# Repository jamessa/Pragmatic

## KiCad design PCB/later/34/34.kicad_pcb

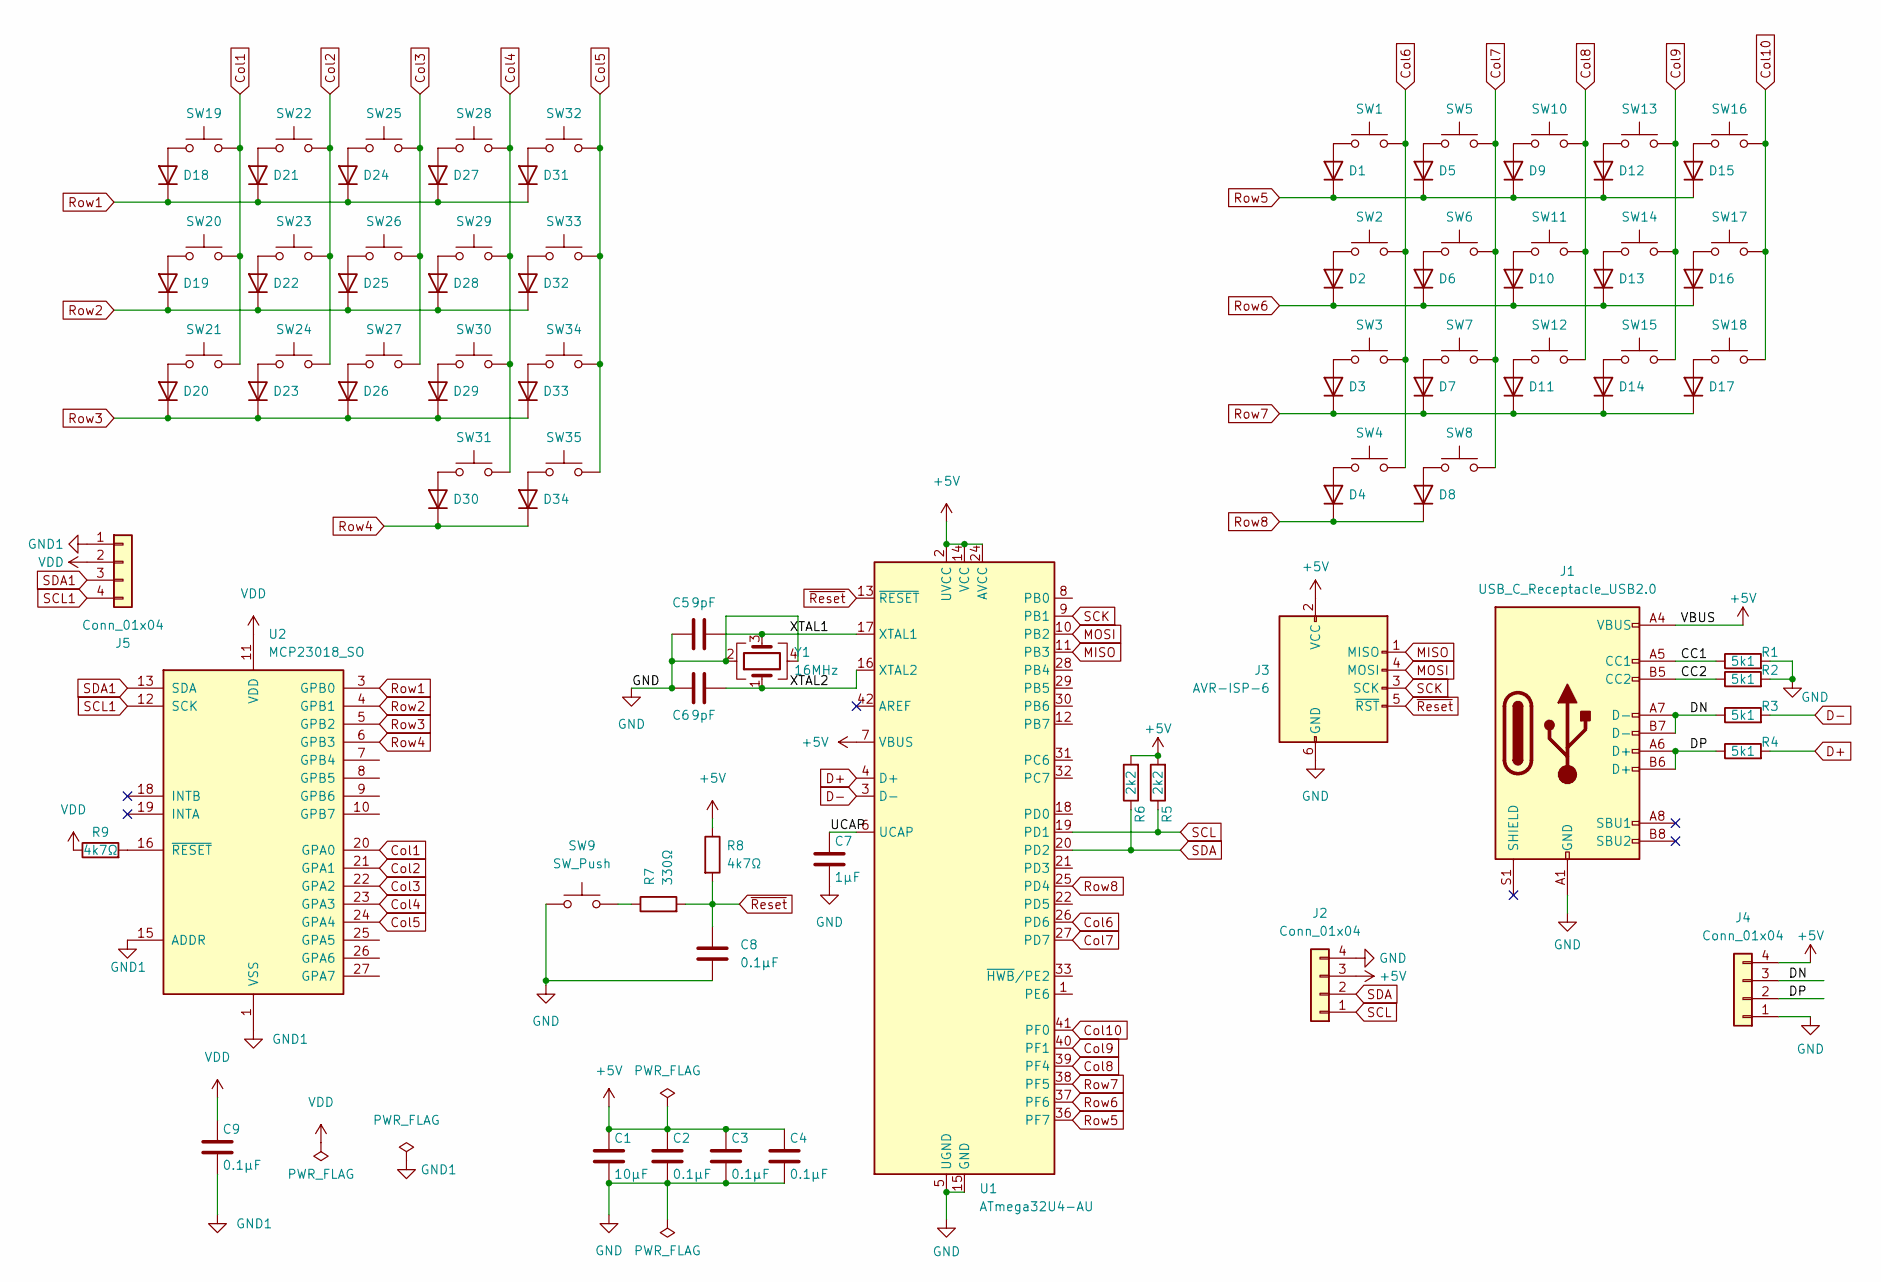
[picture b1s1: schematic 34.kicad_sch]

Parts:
C1: 10µF; C_0603_1608Metric_Pad1.08x0.95mm_HandSolder
C2, C3, C4, C8, C9: 0.1µF; C_0402_1005Metric_Pad0.74x0.62mm_HandSolder
C5, C6: 9pF; C_0402_1005Metric_Pad0.74x0.62mm_HandSolder
C7: 1µF; C_0402_1005Metric_Pad0.74x0.62mm_HandSolder
D1, D2, D3, D4, D5, D6, D7, D8, D9, D10, D11, D12, D13, D14, D15, D16, D17, D18, D19, D20, D21, D22, D23, D24, D25, D26, D27, D28, D29, D30, D31, D32, D33, D34: 1N4148; D3_SMD_v2; LCSC C81598
J1: USB_C_Receptacle_USB2.0; USB_C_Receptacle_HRO_TYPE-C-31-M-12; LCSC C165948
J2, J5: Conn_01x04; JST_PH_S4B-PH-K_1x04_P2.00mm_Horizontal; LCSC C265452
J3: AVR-ISP-6; PinHeader_2x03_P2.54mm_Vertical
J4: Conn_01x04; USB wire pad
R1, R2, R3, R4: 5k1; R_0402_1005Metric_Pad0.72x0.64mm_HandSolder
R5, R6: 2k2; R_0402_1005Metric_Pad0.72x0.64mm_HandSolder
R7: 330Ω; R_0402_1005Metric_Pad0.72x0.64mm_HandSolder
R8, R9: 4k7Ω; R_0402_1005Metric_Pad0.72x0.64mm_HandSolder
SW1, SW2, SW3, SW4, SW5, SW6, SW7, SW8, SW10, SW11, SW12, SW13, SW14, SW15, SW16, SW17, SW18, SW19, SW20, SW21, SW22, SW23, SW24, SW25, SW26, SW27, SW28, SW29, SW30, SW31, SW32, SW33, SW34, SW35: SW_Push; MX_Hotswap_Choc_Solder
SW9: SW_Push; SW_SPST_SKQG_WithStem
U1: ATmega32U4-AU; TQFP-44_10x10mm_P0.8mm
U2: MCP23018_SO; SOIC-28W_7.5x17.9mm_P1.27mm
Y1: 16MHz; Crystal_SMD_3225-4Pin_3.2x2.5mm; LCSC C13738

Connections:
+5V: C1.1, C2.1, C3.1, C4.1, J1.A4 (VBUS), J1.A9 (VBUS), J1.B4 (VBUS), J1.B9 (VBUS), J2.3, J3.2 (VCC), J4.4, R5.2, R6.2, R8.1, U1.2 (UVCC), U1.7 (VBUS), U1.14 (VCC), U1.24 (AVCC), U1.34 (VCC), U1.44 (AVCC)
/CC1: J1.A5 (CC1), R1.1
/CC2: J1.B5 (CC2), R2.1
/DN: J1.A7 (D-), J1.B7 (D-), J4.3, R3.1
/DP: J1.A6 (D+), J1.B6 (D+), J4.2, R4.1
/UCAP: C7.1, U1.6 (UCAP)
/XTAL1: C5.2, U1.17 (XTAL1), Y1.3
/XTAL2: C6.2, U1.16 (XTAL2), Y1.1
Col1: SW19.2, SW20.2, SW21.2, U2.20 (GPA0)
Col2: SW22.2, SW23.2, SW24.2, U2.21 (GPA1)
Col3: SW25.2, SW26.2, SW27.2, U2.22 (GPA2)
Col4: SW28.2, SW29.2, SW30.2, SW31.2, U2.23 (GPA3)
Col5: SW32.2, SW33.2, SW34.2, SW35.2, U2.24 (GPA4)
Col6: SW1.2, SW2.2, SW3.2, SW4.2, U1.26 (PD6)
Col7: SW5.2, SW6.2, SW7.2, SW8.2, U1.27 (PD7)
Col8: SW10.2, SW11.2, SW12.2, U1.39 (PF4)
Col9: SW13.2, SW14.2, SW15.2, U1.40 (PF1)
Col10: SW16.2, SW17.2, SW18.2, U1.41 (PF0)
D+: R4.2, U1.4 (D+)
D-: R3.2, U1.3 (D-)
GND: C1.2, C2.2, C3.2, C4.2, C5.1, C6.1, C7.2, C8.2, J1.A1 (GND), J1.A12 (GND), J1.B1 (GND), J1.B12 (GND), J2.4, J3.6 (GND), J4.1, R1.2, R2.2, SW9.1, U1.5 (UGND), U1.15 (GND), U1.23 (GND), U1.35 (GND), U1.43 (GND), Y1.2, Y1.4
GND1: C9.2, J5.1, U2.1 (VSS), U2.15 (ADDR)
MISO: J3.1 (MISO), U1.11 (PB3)
MOSI: J3.4 (MOSI), U1.10 (PB2)
unnamed: D1.2 (A), SW1.1
unnamed: D2.2 (A), SW2.1
unnamed: D3.2 (A), SW3.1
unnamed: D4.2 (A), SW4.1
unnamed: D5.2 (A), SW5.1
unnamed: D6.2 (A), SW6.1
unnamed: D7.2 (A), SW7.1
unnamed: D8.2 (A), SW8.1
unnamed: D9.2 (A), SW10.1
unnamed: D10.2 (A), SW11.1
unnamed: D11.2 (A), SW12.1
unnamed: D12.2 (A), SW13.1
unnamed: D13.2 (A), SW14.1
unnamed: D14.2 (A), SW15.1
unnamed: D15.2 (A), SW16.1
unnamed: D16.2 (A), SW17.1
unnamed: D17.2 (A), SW18.1
unnamed: D18.2 (A), SW19.1
unnamed: D19.2 (A), SW20.1
unnamed: D20.2 (A), SW21.1
unnamed: D21.2 (A), SW22.1
unnamed: D22.2 (A), SW23.1
unnamed: D23.2 (A), SW24.1
unnamed: D24.2 (A), SW25.1
unnamed: D25.2 (A), SW26.1
unnamed: D26.2 (A), SW27.1
unnamed: D27.2 (A), SW28.1
unnamed: D28.2 (A), SW29.1
unnamed: D29.2 (A), SW30.1
unnamed: D30.2 (A), SW31.1
unnamed: D31.2 (A), SW32.1
unnamed: D32.2 (A), SW33.1
unnamed: D33.2 (A), SW34.1
unnamed: D34.2 (A), SW35.1
unnamed: R7.1, SW9.2
unnamed: R9.2, U2.16 (~RESET)
Row1: D18.1 (K), D21.1 (K), D24.1 (K), D27.1 (K), D31.1 (K), U2.3 (GPB0)
Row2: D19.1 (K), D22.1 (K), D25.1 (K), D28.1 (K), D32.1 (K), U2.4 (GPB1)
Row3: D20.1 (K), D23.1 (K), D26.1 (K), D29.1 (K), D33.1 (K), U2.5 (GPB2)
Row4: D30.1 (K), D34.1 (K), U2.6 (GPB3)
Row5: D1.1 (K), D5.1 (K), D9.1 (K), D12.1 (K), D15.1 (K), U1.36 (PF7)
Row6: D2.1 (K), D6.1 (K), D10.1 (K), D13.1 (K), D16.1 (K), U1.37 (PF6)
Row7: D3.1 (K), D7.1 (K), D11.1 (K), D14.1 (K), D17.1 (K), U1.38 (PF5)
Row8: D4.1 (K), D8.1 (K), U1.25 (PD4)
SCK: J3.3 (SCK), U1.9 (PB1)
SCL: J2.1, R6.1, U1.19 (PD1)
SCL1: J5.4, U2.12 (SCK)
SDA: J2.2, R5.1, U1.20 (PD2)
SDA1: J5.3, U2.13 (SDA)
VDD: C9.1, J5.2, R9.1, U2.11 (VDD)
~Reset: C8.1, J3.5 (~RST), R7.2, R8.2, U1.13 (~RESET)

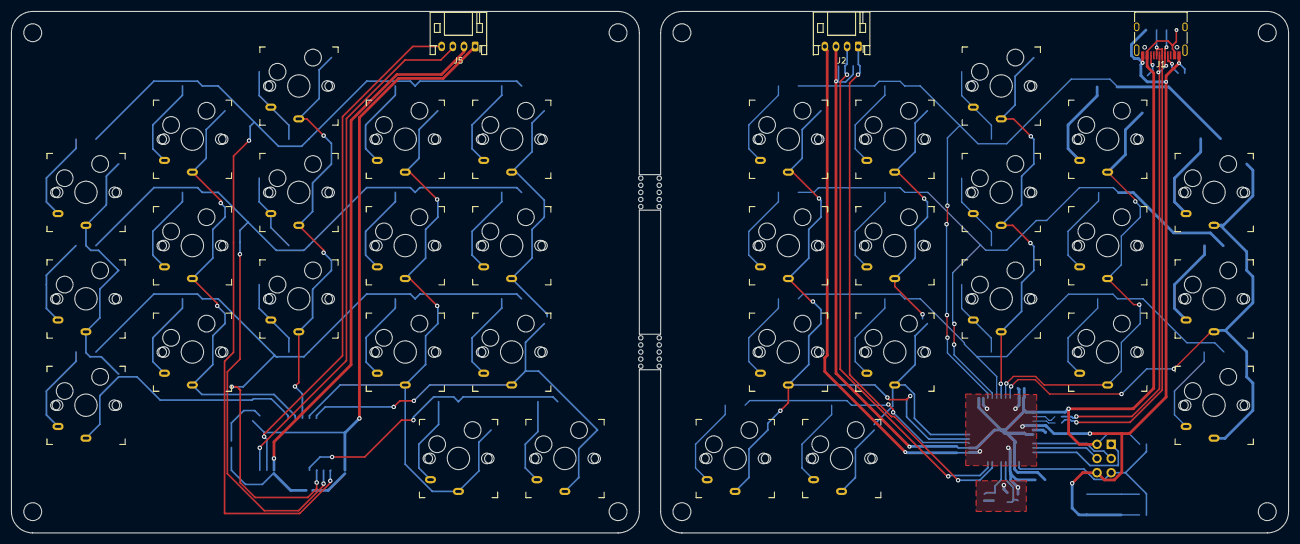
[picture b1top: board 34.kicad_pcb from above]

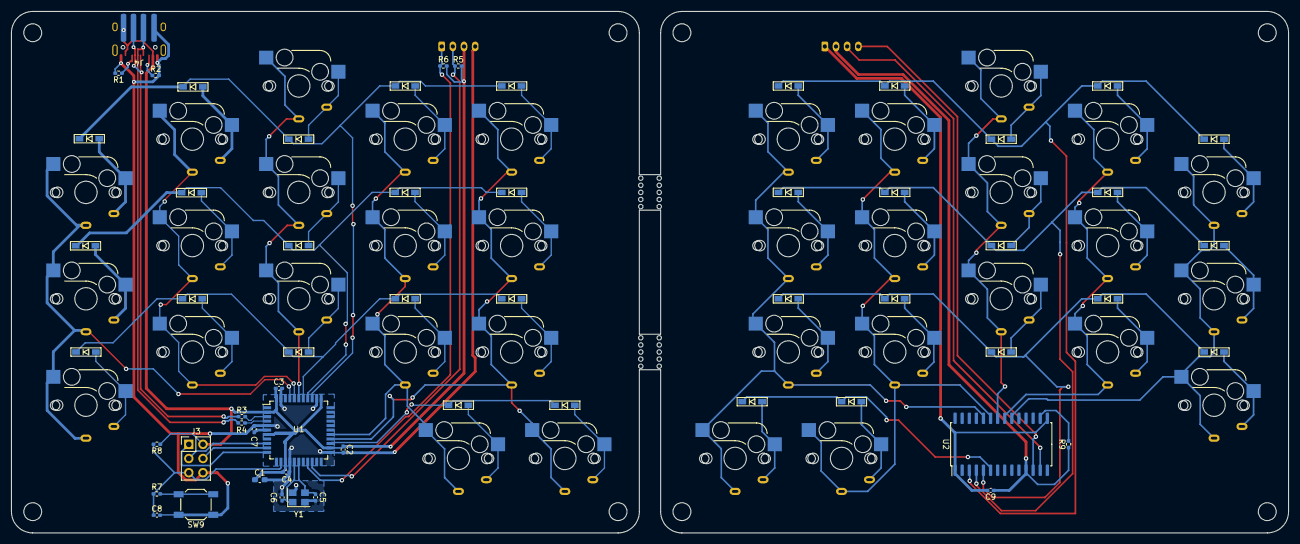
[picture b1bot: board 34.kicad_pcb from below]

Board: 2 copper layers, 228.6 x 93.3 mm, 95 parts (58 on the bottom side), 75 nets.

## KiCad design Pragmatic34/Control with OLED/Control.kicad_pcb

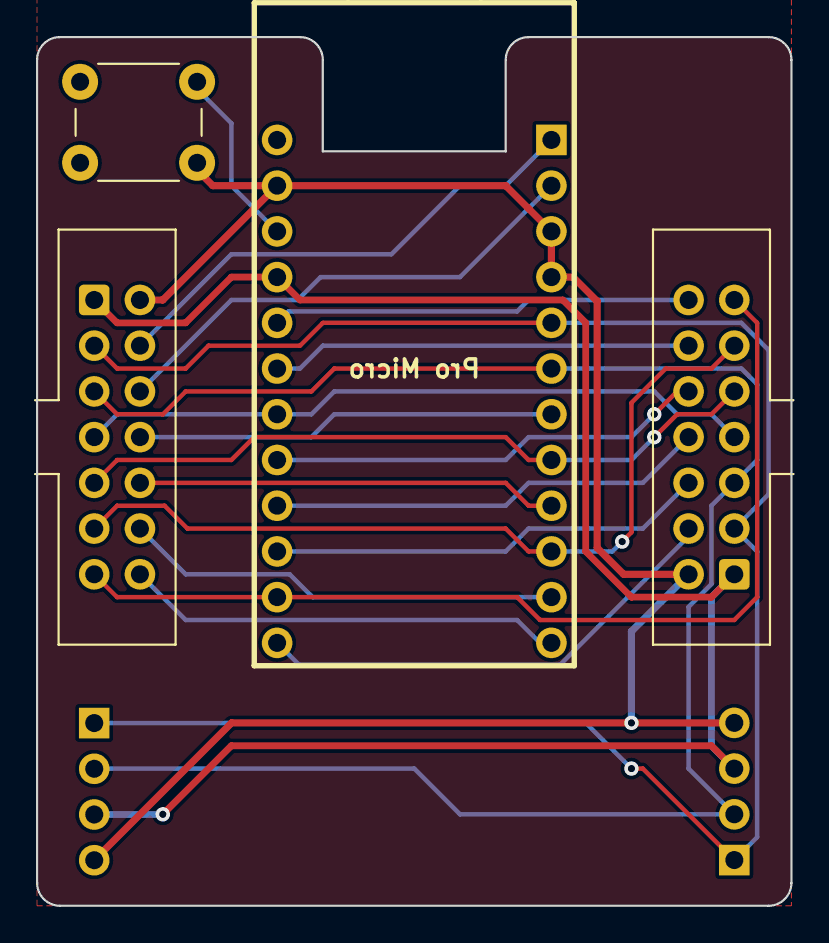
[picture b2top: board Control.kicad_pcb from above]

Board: 2 copper layers, 41.9 x 48.3 mm, 8 parts (1 on the bottom side), 21 nets.

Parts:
J1: L; IDC-Header_2x07_P2.54mm_Vertical
J2: R; IDC-Header_2x07_P2.54mm_Vertical
J3, J4: OLED; SSD1306_OLED-0.91-128x32
L1: JLC Legend
Logo1: OSHW-Symbol_6.7x6mm_Copper
SW1: SW_Push; SW_PUSH_6mm
U1: ProMicro; ProMicro Type C Reversed

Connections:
Col1: J1.4, U1.1 (TX0/PD3)
Col2: J1.6, U1.2 (RX1/PD2)
Col3: J1.8, U1.7 (4/PD4)
Col4: J1.10, U1.9 (6/PD7)
Col5: J1.12, U1.11 (8/PB4)
Col6: J1.14, U1.12 (9/PB5)
Col7: J2.4, U1.13 (10/PB6)
Col8: J2.6, U1.15 (14/PB3)
Col9: J2.8, U1.16 (15/PB1)
Col10: J2.10, U1.17 (A0/PF7)
Col11: J2.12, U1.19 (A2/PF5)
Col12: J2.14, U1.20 (A3/PF4)
GND: J1.2, J2.2, J3.4, J4.4, SW1.2, U1.3 (GND), U1.4 (GND), U1.23 (GND)
Reset: SW1.1, U1.22 (RST)
Row1: J1.3, J2.3, J3.1, J4.1, U1.5 (2/PD1)
Row2: J1.5, J2.5, J3.2, J4.2, U1.6 (3/PD0)
Row3: J1.7, J2.7, U1.18 (A1/PF6)
Row4: J1.9, J2.9, U1.8 (5/PC6)
Row5: J1.11, J2.11, U1.10 (7/PE6)
Row6: J1.13, J2.13, U1.14 (16/PB2)
VCC: J1.1, J2.1, J3.3, J4.3, U1.21 (VCC)

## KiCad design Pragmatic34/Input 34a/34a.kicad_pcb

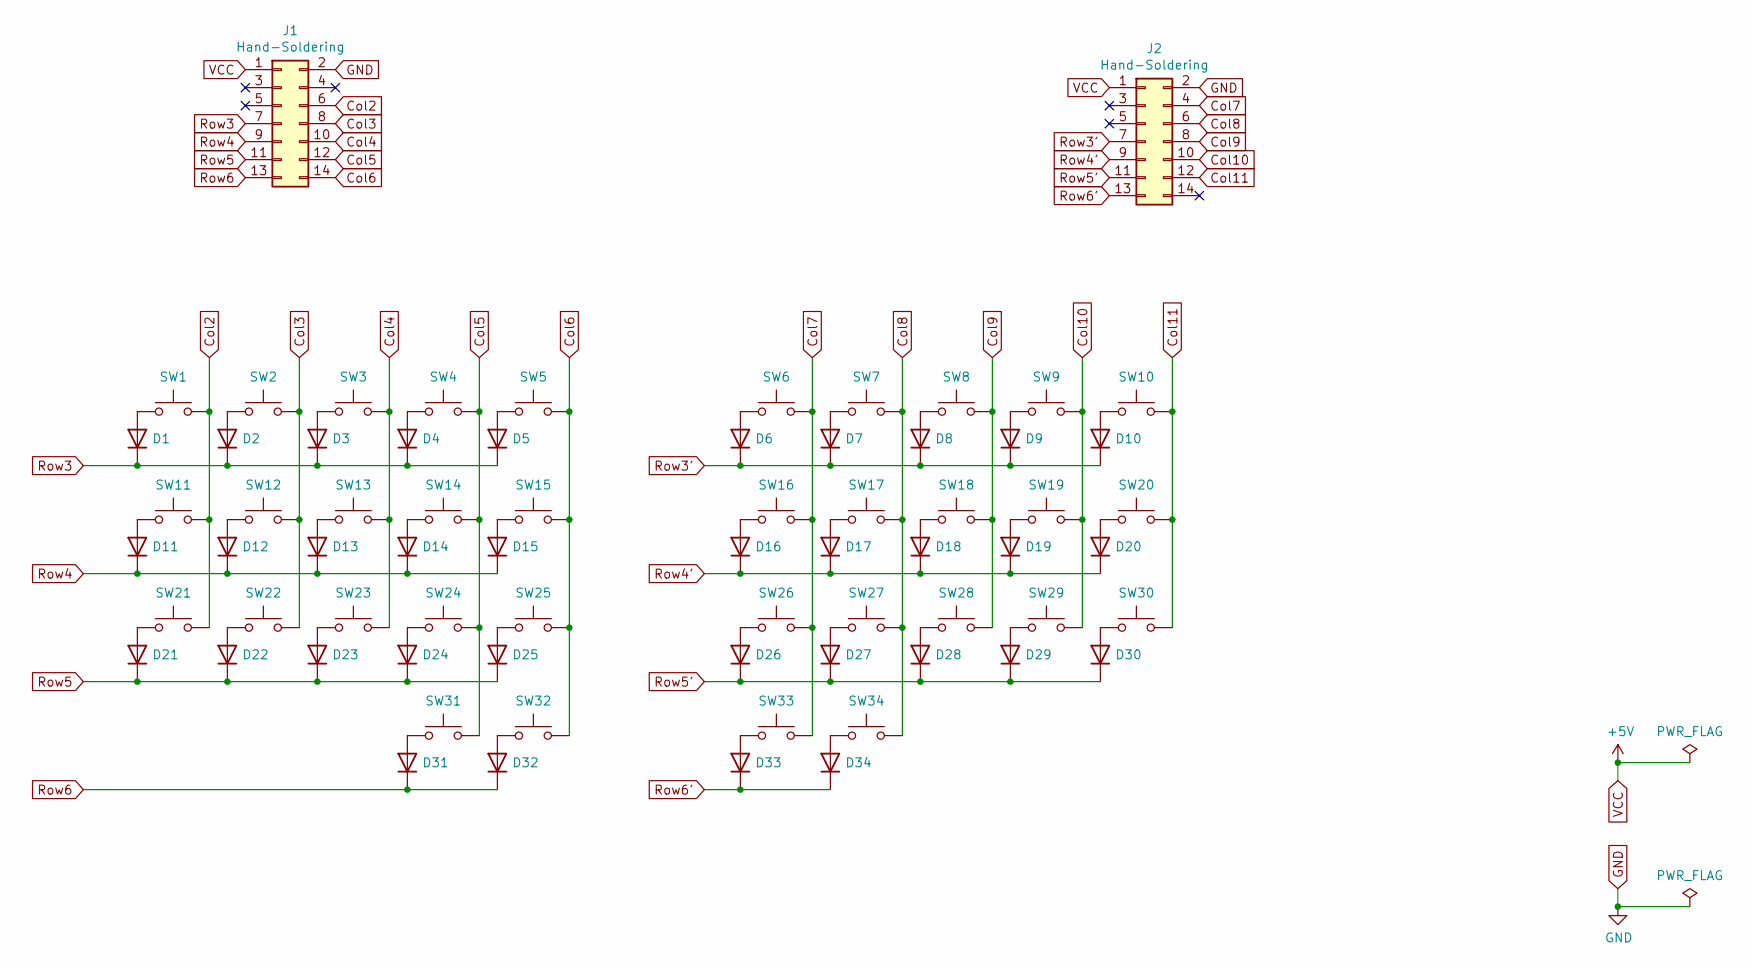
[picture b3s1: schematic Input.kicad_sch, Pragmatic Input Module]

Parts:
D1, D2, D3, D4, D5, D6, D7, D8, D9, D10, D11, D12, D13, D14, D15, D16, D17, D18, D19, D20, D21, D22, D23, D24, D25, D26, D27, D28, D29, D30, D31, D32, D33, D34: 1N4148; D3_SMD_v2; LCSC C81598
J1, J2: Hand-Soldering; IDC-Header_2x07_P2.54mm_Vertical; LCSC C3406
SW1, SW2, SW3, SW4, SW5, SW6, SW7, SW8, SW9, SW10, SW11, SW12, SW13, SW14, SW15, SW16, SW17, SW18, SW19, SW20, SW21, SW22, SW23, SW24, SW25, SW26, SW27, SW28, SW29, SW30, SW31, SW32, SW33, SW34: SW_Push; MX_Hotswap; LCSC C2803348

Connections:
Col2: J1.6, SW1.2, SW11.2, SW21.2
Col3: J1.8, SW2.2, SW12.2, SW22.2
Col4: J1.10, SW3.2, SW13.2, SW23.2; also elsewhere on the board
Col5: J1.12, SW4.2, SW14.2, SW24.2, SW31.2
Col6: J1.14, SW5.2, SW15.2, SW25.2, SW32.2
Col7: J2.4, SW6.2, SW16.2, SW26.2, SW33.2
Col8: J2.6, SW7.2, SW17.2, SW27.2, SW34.2
Col9: J2.8, SW8.2, SW18.2, SW28.2; also elsewhere on the board
Col10: J2.10, SW9.2, SW19.2, SW29.2
Col11: J2.12, SW10.2, SW20.2, SW30.2
GND: J1.2, J2.2
unnamed: D1.2 (A), SW1.1
unnamed: D2.2 (A), SW2.1
unnamed: D3.2 (A), SW3.1
unnamed: D4.2 (A), SW4.1
unnamed: D5.2 (A), SW5.1
unnamed: D6.2 (A), SW6.1
unnamed: D7.2 (A), SW7.1
unnamed: D8.2 (A), SW8.1
unnamed: D9.2 (A), SW9.1
unnamed: D10.2 (A), SW10.1
unnamed: D11.2 (A), SW11.1
unnamed: D12.2 (A), SW12.1
unnamed: D13.2 (A), SW13.1
unnamed: D14.2 (A), SW14.1
unnamed: D15.2 (A), SW15.1
unnamed: D16.2 (A), SW16.1
unnamed: D17.2 (A), SW17.1
unnamed: D18.2 (A), SW18.1
unnamed: D19.2 (A), SW19.1
unnamed: D20.2 (A), SW20.1
unnamed: D21.2 (A), SW21.1
unnamed: D22.2 (A), SW22.1
unnamed: D23.2 (A), SW23.1
unnamed: D24.2 (A), SW24.1
unnamed: D25.2 (A), SW25.1
unnamed: D26.2 (A), SW26.1
unnamed: D27.2 (A), SW27.1
unnamed: D28.2 (A), SW28.1
unnamed: D29.2 (A), SW29.1
unnamed: D30.2 (A), SW30.1
unnamed: D31.2 (A), SW31.1
unnamed: D32.2 (A), SW32.1
unnamed: D33.2 (A), SW33.1
unnamed: D34.2 (A), SW34.1
Row3: D1.1 (K), D2.1 (K), D3.1 (K), D4.1 (K), D5.1 (K), J1.7
Row3': D6.1 (K), D7.1 (K), D8.1 (K), D9.1 (K), D10.1 (K), J2.7
Row4: D11.1 (K), D12.1 (K), D13.1 (K), D14.1 (K), D15.1 (K), J1.9
Row4': D16.1 (K), D17.1 (K), D18.1 (K), D19.1 (K), D20.1 (K), J2.9
Row5: D21.1 (K), D22.1 (K), D23.1 (K), D24.1 (K), D25.1 (K), J1.11
Row5': D26.1 (K), D27.1 (K), D28.1 (K), D29.1 (K), D30.1 (K), J2.11
Row6: D31.1 (K), D32.1 (K), J1.13; also elsewhere on the board
Row6': D33.1 (K), D34.1 (K), J2.13; also elsewhere on the board
VCC: J1.1, J2.1

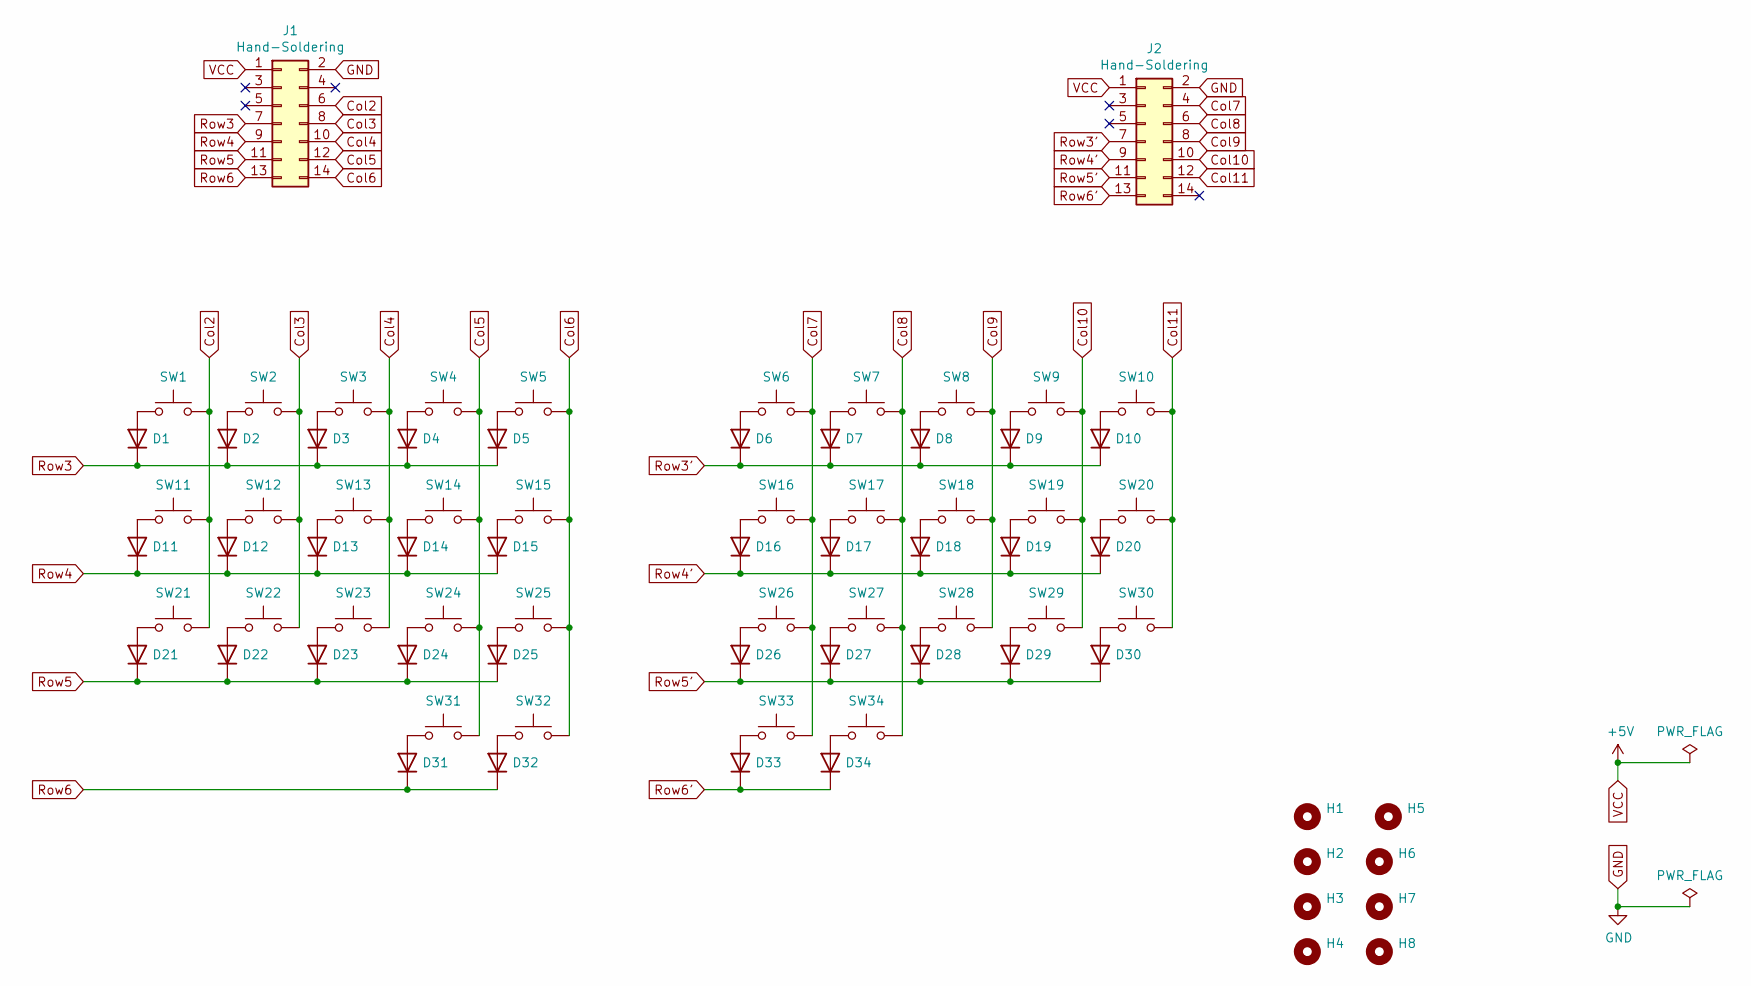
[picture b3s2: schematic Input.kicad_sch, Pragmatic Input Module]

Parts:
D1, D2, D3, D4, D5, D6, D7, D8, D9, D10, D11, D12, D13, D14, D15, D16, D17, D18, D19, D20, D21, D22, D23, D24, D25, D26, D27, D28, D29, D30, D31, D32, D33, D34: 1N4148; D3_SMD_v2; LCSC C81598
H1, H2, H3, H4, H5, H6, H7, H8: MountingHole; MountingHole_2.5mm
J1, J2: Hand-Soldering; IDC-Header_2x07_P2.54mm_Vertical; LCSC C3406
SW1, SW2, SW3, SW4, SW5, SW6, SW7, SW8, SW9, SW10, SW11, SW12, SW13, SW14, SW15, SW16, SW17, SW18, SW19, SW20, SW21, SW22, SW23, SW24, SW25, SW26, SW27, SW28, SW29, SW30, SW31, SW32, SW33, SW34: SW_Push; MX_Hotswap; LCSC C2803348

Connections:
Col2: J1.6, SW1.2, SW11.2, SW21.2
Col3: J1.8, SW2.2, SW12.2, SW22.2
Col4: J1.10, SW3.2, SW13.2, SW23.2; also elsewhere on the board
Col5: J1.12, SW4.2, SW14.2, SW24.2, SW31.2
Col6: J1.14, SW5.2, SW15.2, SW25.2, SW32.2
Col7: J2.4, SW6.2, SW16.2, SW26.2, SW33.2
Col8: J2.6, SW7.2, SW17.2, SW27.2, SW34.2
Col9: J2.8, SW8.2, SW18.2, SW28.2; also elsewhere on the board
Col10: J2.10, SW9.2, SW19.2, SW29.2
Col11: J2.12, SW10.2, SW20.2, SW30.2
GND: J1.2, J2.2
unnamed: D1.2 (A), SW1.1
unnamed: D2.2 (A), SW2.1
unnamed: D3.2 (A), SW3.1
unnamed: D4.2 (A), SW4.1
unnamed: D5.2 (A), SW5.1
unnamed: D6.2 (A), SW6.1
unnamed: D7.2 (A), SW7.1
unnamed: D8.2 (A), SW8.1
unnamed: D9.2 (A), SW9.1
unnamed: D10.2 (A), SW10.1
unnamed: D11.2 (A), SW11.1
unnamed: D12.2 (A), SW12.1
unnamed: D13.2 (A), SW13.1
unnamed: D14.2 (A), SW14.1
unnamed: D15.2 (A), SW15.1
unnamed: D16.2 (A), SW16.1
unnamed: D17.2 (A), SW17.1
unnamed: D18.2 (A), SW18.1
unnamed: D19.2 (A), SW19.1
unnamed: D20.2 (A), SW20.1
unnamed: D21.2 (A), SW21.1
unnamed: D22.2 (A), SW22.1
unnamed: D23.2 (A), SW23.1
unnamed: D24.2 (A), SW24.1
unnamed: D25.2 (A), SW25.1
unnamed: D26.2 (A), SW26.1
unnamed: D27.2 (A), SW27.1
unnamed: D28.2 (A), SW28.1
unnamed: D29.2 (A), SW29.1
unnamed: D30.2 (A), SW30.1
unnamed: D31.2 (A), SW31.1
unnamed: D32.2 (A), SW32.1
unnamed: D33.2 (A), SW33.1
unnamed: D34.2 (A), SW34.1
Row3: D1.1 (K), D2.1 (K), D3.1 (K), D4.1 (K), D5.1 (K), J1.7
Row3': D6.1 (K), D7.1 (K), D8.1 (K), D9.1 (K), D10.1 (K), J2.7
Row4: D11.1 (K), D12.1 (K), D13.1 (K), D14.1 (K), D15.1 (K), J1.9
Row4': D16.1 (K), D17.1 (K), D18.1 (K), D19.1 (K), D20.1 (K), J2.9
Row5: D21.1 (K), D22.1 (K), D23.1 (K), D24.1 (K), D25.1 (K), J1.11
Row5': D26.1 (K), D27.1 (K), D28.1 (K), D29.1 (K), D30.1 (K), J2.11
Row6: D31.1 (K), D32.1 (K), J1.13; also elsewhere on the board
Row6': D33.1 (K), D34.1 (K), J2.13; also elsewhere on the board
VCC: J1.1, J2.1

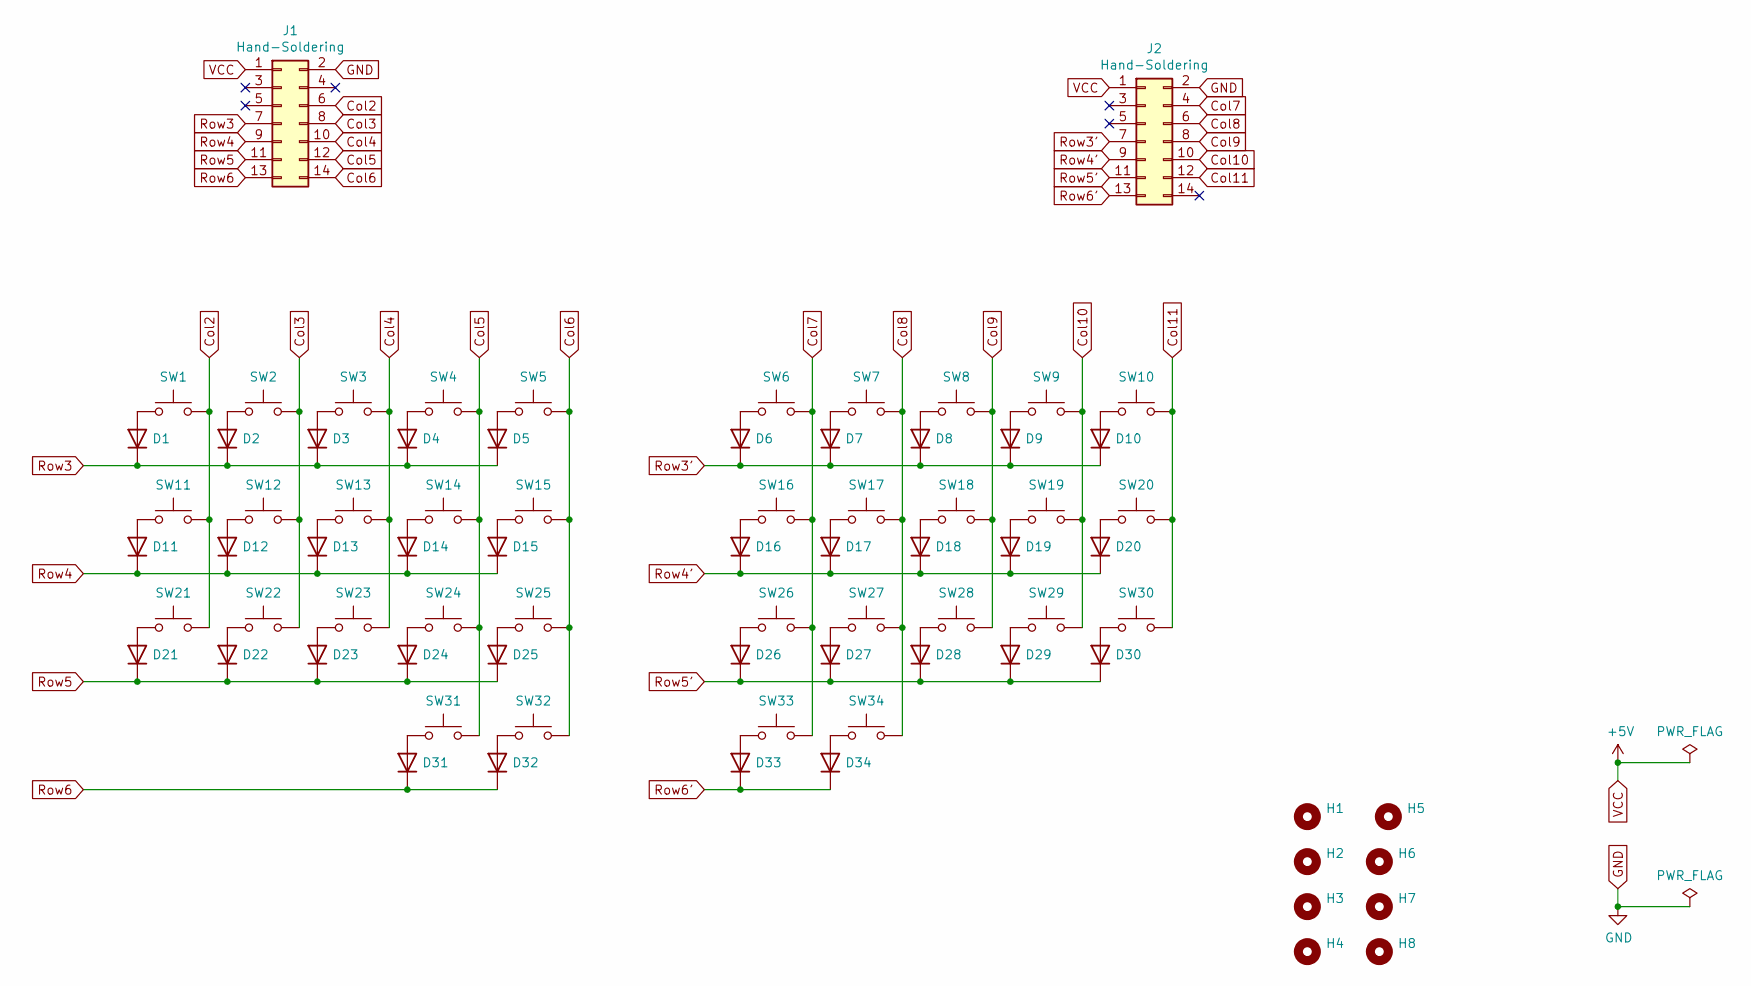
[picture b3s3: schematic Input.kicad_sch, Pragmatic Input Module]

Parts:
D1, D2, D3, D4, D5, D6, D7, D8, D9, D10, D11, D12, D13, D14, D15, D16, D17, D18, D19, D20, D21, D22, D23, D24, D25, D26, D27, D28, D29, D30, D31, D32, D33, D34: 1N4148; D3_SMD_v2; LCSC C81598
H1, H2, H3, H4, H5, H6, H7, H8: MountingHole; MountingHole_2.5mm
J1, J2: Hand-Soldering; IDC-Header_2x07_P2.54mm_Vertical; LCSC C3406
SW1, SW2, SW3, SW4, SW5, SW6, SW7, SW8, SW9, SW10, SW11, SW12, SW13, SW14, SW15, SW16, SW17, SW18, SW19, SW20, SW21, SW22, SW23, SW24, SW25, SW26, SW27, SW28, SW29, SW30, SW31, SW32, SW33, SW34: SW_Push; MX_Hotswap

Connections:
Col2: J1.6, SW1.2, SW11.2, SW21.2
Col3: J1.8, SW2.2, SW12.2, SW22.2
Col4: J1.10, SW3.2, SW13.2, SW23.2; also elsewhere on the board
Col5: J1.12, SW4.2, SW14.2, SW24.2, SW31.2
Col6: J1.14, SW5.2, SW15.2, SW25.2, SW32.2
Col7: J2.4, SW6.2, SW16.2, SW26.2, SW33.2
Col8: J2.6, SW7.2, SW17.2, SW27.2, SW34.2
Col9: J2.8, SW8.2, SW18.2, SW28.2; also elsewhere on the board
Col10: J2.10, SW9.2, SW19.2, SW29.2
Col11: J2.12, SW10.2, SW20.2, SW30.2
GND: J1.2, J2.2
unnamed: D1.2 (A), SW1.1
unnamed: D2.2 (A), SW2.1
unnamed: D3.2 (A), SW3.1
unnamed: D4.2 (A), SW4.1
unnamed: D5.2 (A), SW5.1
unnamed: D6.2 (A), SW6.1
unnamed: D7.2 (A), SW7.1
unnamed: D8.2 (A), SW8.1
unnamed: D9.2 (A), SW9.1
unnamed: D10.2 (A), SW10.1
unnamed: D11.2 (A), SW11.1
unnamed: D12.2 (A), SW12.1
unnamed: D13.2 (A), SW13.1
unnamed: D14.2 (A), SW14.1
unnamed: D15.2 (A), SW15.1
unnamed: D16.2 (A), SW16.1
unnamed: D17.2 (A), SW17.1
unnamed: D18.2 (A), SW18.1
unnamed: D19.2 (A), SW19.1
unnamed: D20.2 (A), SW20.1
unnamed: D21.2 (A), SW21.1
unnamed: D22.2 (A), SW22.1
unnamed: D23.2 (A), SW23.1
unnamed: D24.2 (A), SW24.1
unnamed: D25.2 (A), SW25.1
unnamed: D26.2 (A), SW26.1
unnamed: D27.2 (A), SW27.1
unnamed: D28.2 (A), SW28.1
unnamed: D29.2 (A), SW29.1
unnamed: D30.2 (A), SW30.1
unnamed: D31.2 (A), SW31.1
unnamed: D32.2 (A), SW32.1
unnamed: D33.2 (A), SW33.1
unnamed: D34.2 (A), SW34.1
Row3: D1.1 (K), D2.1 (K), D3.1 (K), D4.1 (K), D5.1 (K), J1.7
Row3': D6.1 (K), D7.1 (K), D8.1 (K), D9.1 (K), D10.1 (K), J2.7
Row4: D11.1 (K), D12.1 (K), D13.1 (K), D14.1 (K), D15.1 (K), J1.9
Row4': D16.1 (K), D17.1 (K), D18.1 (K), D19.1 (K), D20.1 (K), J2.9
Row5: D21.1 (K), D22.1 (K), D23.1 (K), D24.1 (K), D25.1 (K), J1.11
Row5': D26.1 (K), D27.1 (K), D28.1 (K), D29.1 (K), D30.1 (K), J2.11
Row6: D31.1 (K), D32.1 (K), J1.13; also elsewhere on the board
Row6': D33.1 (K), D34.1 (K), J2.13; also elsewhere on the board
VCC: J1.1, J2.1

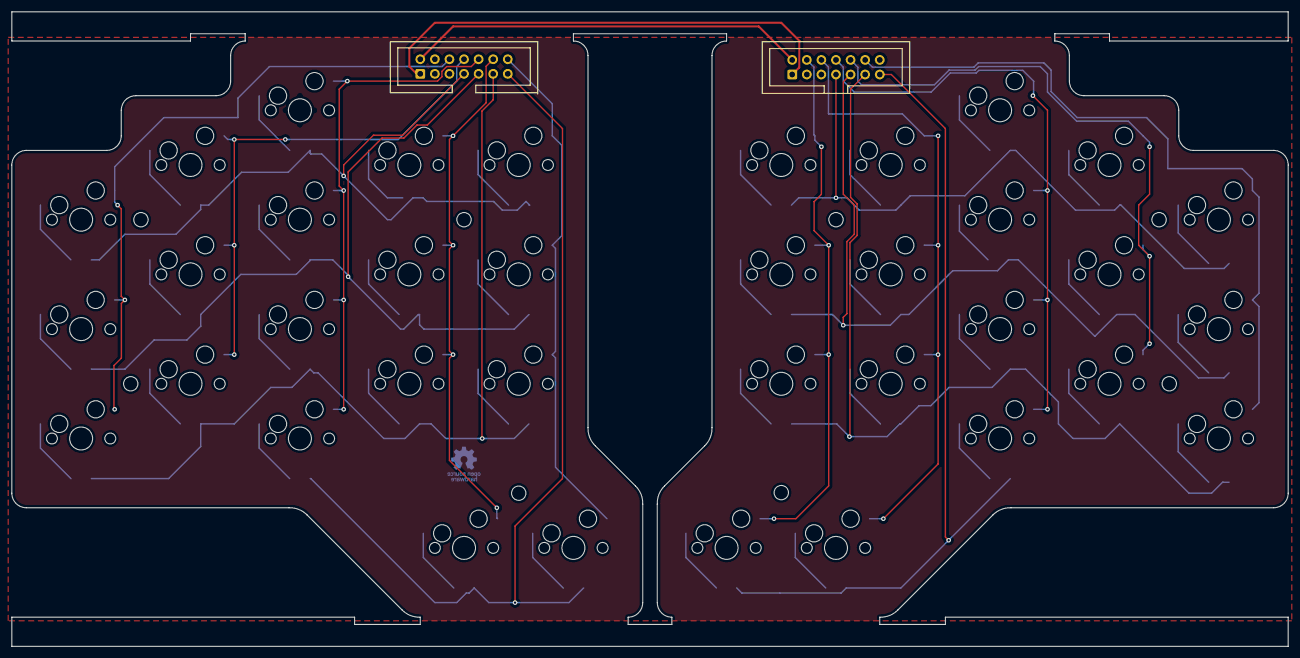
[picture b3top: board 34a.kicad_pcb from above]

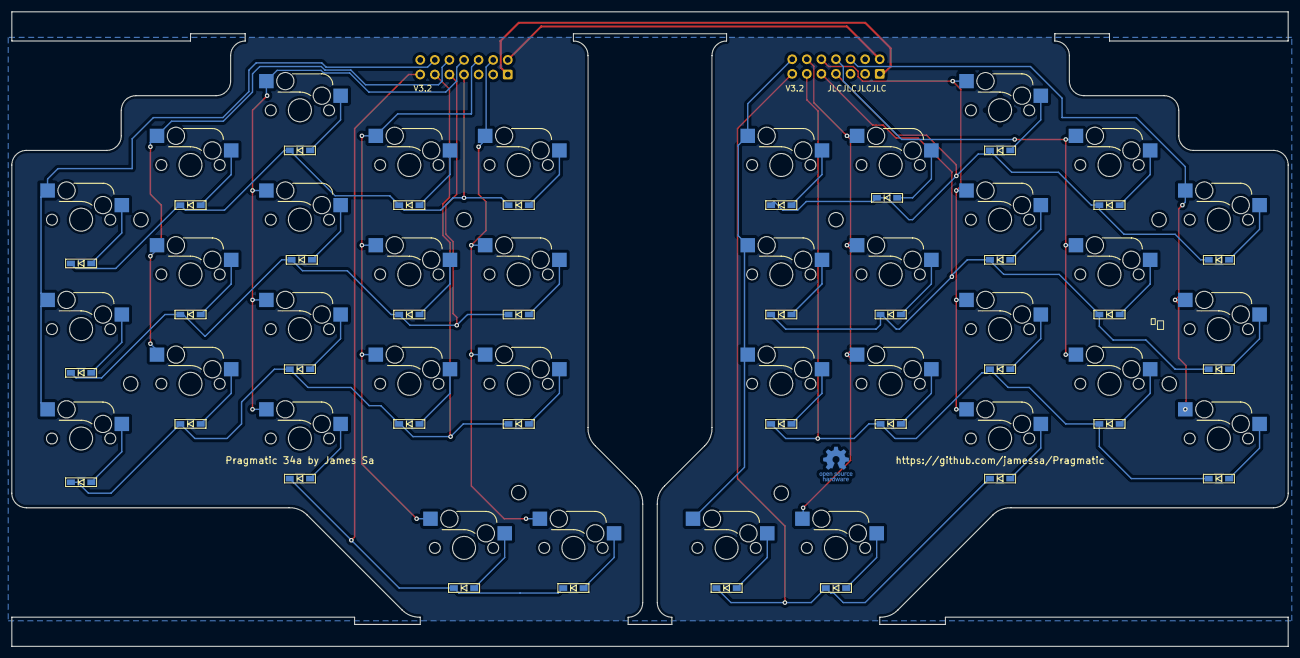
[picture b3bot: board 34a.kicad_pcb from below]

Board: 2 copper layers, 222.2 x 110.5 mm, 83 parts (37 on the bottom side), 56 nets.

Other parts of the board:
D37, D38: 1N4148; D3_SMD_v2
LOGO1: Logo_Open_Hardware_Small; OSHW-Logo_5.7x6mm_Copper
SW37, SW38: SW_Push; MX_Hotswap

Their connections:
Col4: SW37.2; also elsewhere on the board
Col9: SW38.2; also elsewhere on the board
unnamed: D37.2 (A), SW37.1
unnamed: D38.2 (A), SW38.1
Row6: D37.1 (K); also elsewhere on the board
Row6': D38.1 (K); also elsewhere on the board

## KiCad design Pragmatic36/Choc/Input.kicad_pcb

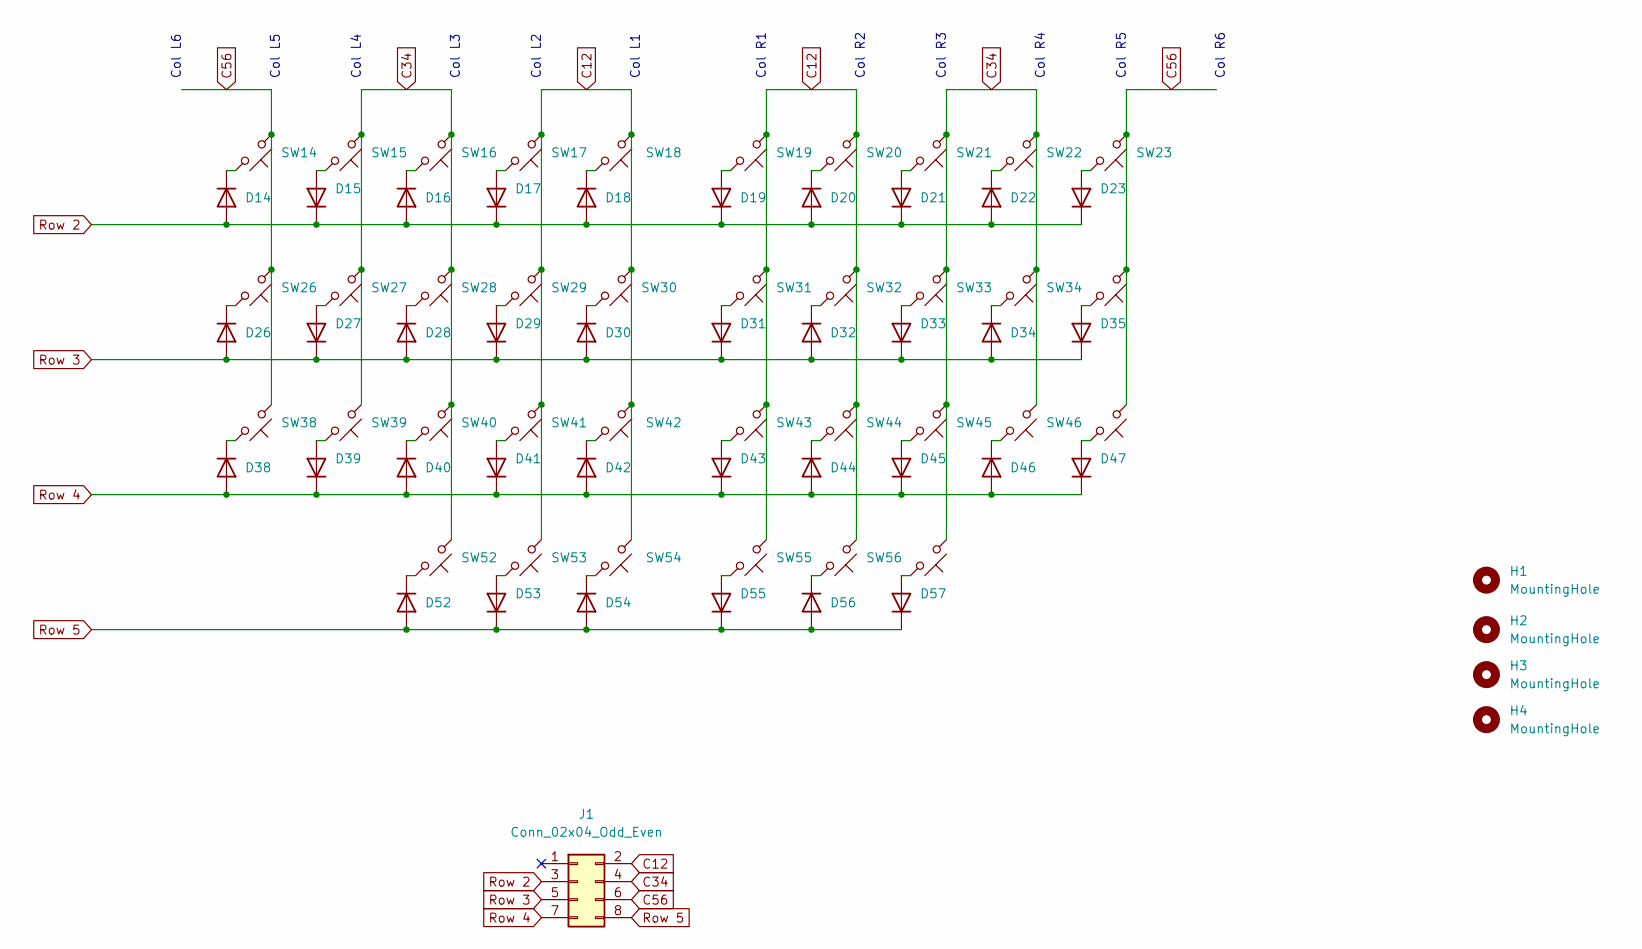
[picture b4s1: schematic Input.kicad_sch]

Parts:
D14, D15, D16, D17, D18, D19, D20, D21, D22, D23, D26, D27, D28, D29, D30, D31, D32, D33, D34, D35, D38, D39, D40, D41, D42, D43, D44, D45, D46, D47, D52, D53, D54, D55, D56, D57: 1N4448W; D3_SMD_v2
H1, H2, H3, H4: MountingHole; MountingHole_3.2mm_M3_DIN965
J1: Conn_02x04_Odd_Even; matrix_connector
SW14, SW15, SW16, SW17, SW18, SW26, SW27, SW28, SW29, SW30, SW38, SW39, SW40, SW41, SW42, SW52, SW53, SW54: SW_Push_45deg; ChocV1_Hotswap_reverse
SW19, SW20, SW21, SW22, SW23, SW31, SW32, SW33, SW34, SW35, SW43, SW44, SW45, SW46, SW47, SW55, SW56, SW57: SW_Push_45deg; ChocV1_Hotswap

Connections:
C12: J1.2, SW17.1, SW18.1, SW19.1, SW20.1, SW29.1, SW30.1, SW31.1, SW32.1, SW41.1, SW42.1, SW43.1, SW44.1, SW53.1, SW54.1, SW55.1, SW56.1
C34: J1.4, SW15.1, SW16.1, SW21.1, SW22.1, SW27.1, SW28.1, SW33.1, SW34.1, SW39.1, SW40.1, SW45.1, SW46.1, SW52.1, SW57.1
C56: J1.6, SW14.1, SW23.1, SW26.1, SW35.1, SW38.1, SW47.1
unnamed: D14.1 (K), SW14.2
unnamed: D15.2 (A), SW15.2
unnamed: D16.1 (K), SW16.2
unnamed: D17.2 (A), SW17.2
unnamed: D18.1 (K), SW18.2
unnamed: D19.2 (A), SW19.2
unnamed: D20.1 (K), SW20.2
unnamed: D21.2 (A), SW21.2
unnamed: D22.1 (K), SW22.2
unnamed: D23.2 (A), SW23.2
unnamed: D26.1 (K), SW26.2
unnamed: D27.2 (A), SW27.2
unnamed: D28.1 (K), SW28.2
unnamed: D29.2 (A), SW29.2
unnamed: D30.1 (K), SW30.2
unnamed: D31.2 (A), SW31.2
unnamed: D32.1 (K), SW32.2
unnamed: D33.2 (A), SW33.2
unnamed: D34.1 (K), SW34.2
unnamed: D35.2 (A), SW35.2
unnamed: D38.1 (K), SW38.2
unnamed: D39.2 (A), SW39.2
unnamed: D40.1 (K), SW40.2
unnamed: D41.2 (A), SW41.2
unnamed: D42.1 (K), SW42.2
unnamed: D43.2 (A), SW43.2
unnamed: D44.1 (K), SW44.2
unnamed: D45.2 (A), SW45.2
unnamed: D46.1 (K), SW46.2
unnamed: D47.2 (A), SW47.2
unnamed: D52.1 (K), SW52.2
unnamed: D53.2 (A), SW53.2
unnamed: D54.1 (K), SW54.2
unnamed: D55.2 (A), SW55.2
unnamed: D56.1 (K), SW56.2
unnamed: D57.2 (A), SW57.2
Row 2: D14.2 (A), D15.1 (K), D16.2 (A), D17.1 (K), D18.2 (A), D19.1 (K), D20.2 (A), D21.1 (K), D22.2 (A), D23.1 (K), J1.3
Row 3: D26.2 (A), D27.1 (K), D28.2 (A), D29.1 (K), D30.2 (A), D31.1 (K), D32.2 (A), D33.1 (K), D34.2 (A), D35.1 (K), J1.5
Row 4: D38.2 (A), D39.1 (K), D40.2 (A), D41.1 (K), D42.2 (A), D43.1 (K), D44.2 (A), D45.1 (K), D46.2 (A), D47.1 (K), J1.7
Row 5: D52.2 (A), D53.1 (K), D54.2 (A), D55.1 (K), D56.2 (A), D57.1 (K), J1.8

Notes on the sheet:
Col L4
Col R1
Col L1
Col R5
Col L6
Col R3
Col L3
Col R6
Col L5
Col R2
Col R4
Col L2
